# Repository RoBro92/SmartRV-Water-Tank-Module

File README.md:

# SmartRV Water Tank Module
**A ESP based water tank module for a Camper/RV**

All feature requests are tracked in the GitHub issue tracker. 
[Feature Requests](https://github.com/RoBro92/feature-requests/issues)

This water tank module is designed to fill a gap in the market for accessible smart water tank monitoring. Other systems such as Pico and Victron do exist however their cost can be prohibitive and require additional components. This module is based on the ESP8266/32 by Espressif & is designed to work standalone or as part of a network to provide accurate and real-time updates for water tank level and temperature. It also provides a relay designed to interface with motorized ball valves or 2/3 wire and will allow remote draining of tanks without having to leave the vehicle. This not only makes filling the tank easier but can also provide emergency frost protection. 

The beauty of the ESP32 is that it can be easily programmed and by having the extra pins on a header you can add your own inputs/outputs to interface with the board. 

The module has been kept as compact as possible and allows for a direct connection to 12v or 24v vehicle systems. 

**If you want to support the development you can purchase the V1 board as a DIY kit or fully assembled V2  from my Ko-Fi Shop [SmartRV Shop](https://ko-fi.com/smartrv/shop)**

## **I have developed two separate versions of this module**

[V1 is THT and is suitable for at-home soldering](#tht)

[V2 is the final retail product and comes pre assembled inclduing software to allow easy OTA upload](#smd)

### THT

# **V1.3**
This release represents the final revision any further changes should be requested in the [Feature Requests](https://github.com/RoBro92/feature-requests/issues) section. It has been updated to include the design schematic and PCB layout. I will stock a number of these boards to be assembled by yourself and can also include supporting documentation. This device can also be supplied assembled if required. 

# **Changes**
- [x] - Updated to V1.3 final. 

# **Features**
- [x] - Removeable WemosD1 chip (ESP8266)
- [x] - Onboard power regulation
- [x] - Variable voltage input 8v-36v
- [x] - Compact form factor
- [x] - DS18b20 temperature sensor
- [x] - Resistive water level sensor
- [x] - 10A relay for water valve control
- [x] - LED Indicator for Power-ON
- [x] - Added reverse polarity protection
- [x] - Added LED indicators for power and relay
- [x] - Updated repository with Gerber production files

# **Images**
<table>
  <tr>
    <td>3D Model</td>
  </tr>
  <tr>
    <td></td>
  </tr>
 
 </table>
<table>
  <tr>
         <td>Schematic</td>
     <td>PCB Layout</td>

  </tr>
  <tr>
   <td></td>
   <td></td>    
  </tr>
 </table>

<table>
  <tr>
    <td>PCB Front v1.0</td>
     <td>PCB Rear v1.0</td>
  </tr>
  <tr>
    <td></td>
    <td></td>
  </tr>
 </table>

# **WARNING**
This board does not have any fuse protection as such this must be provided externally.

___

### SMD

# **V2.1**
This version is the final retail production of the SmartRV Water Tank Module. It comes with many improvements over the V1 version. 
Built primarily with surface mounted components this version is able to be as compact as possible while also retaining a full feature set. 
This board will be available to buy from my Kofi Shop.

It will also feature an ESP32 Module for several reasons;
- Bluetooth connection with AIO board to act as an additional wireless tank sensor
- Lower power consumption if being used with a battery
- Newer technology

# **Changes This Version**
- [x] - Added 3D printed case

# **Features**
- [x] - ESP32-C3-Mini
- [x] - Onboard power regulation
- [x] - Variable voltage input 8v-36v
- [x] - Compact form factor
- [x] - DS18b20 temperature sensor input
- [x] - Resistive water level sensor input with variable resistance selection via THT resistor
- [x] - 10A relay for water valve control 
- [x] - Reverse polarity protection
- [x] - External display provided via TX/RX for Nextion display
- [x] - Reverse polarity protection
- [x] - Expansion header for user customisation
- [x] - Bluetooth communication built into ESP32 module

# **Planned Changes**

- [ ] - Bluetooth app
- [ ] - Onboard USB programmer
- [ ] - Manual Override switch

# **Images**
<table>
  <tr>
    <td>Schematic</td>
     <td>PCB Layout</td>
  </tr>
  <tr>
    <td></td>
    <td></td>
  </tr>
 </table>

<table>
  <tr>
    <td>3D Model Front</td>
     <td>3D Model Rear</td>
  </tr>
  <tr>
    <td></td>
    <td></td>
  </tr>
 </table>

<table>
  <tr>
    <td>Case</td>
     <td>Case Inside</td>
  </tr>
  <tr>
    <td></td>
    <td></td>
  </tr>
 </table>

# **WARNING**
This board does not have any fuse protection as such this must be provided externally.

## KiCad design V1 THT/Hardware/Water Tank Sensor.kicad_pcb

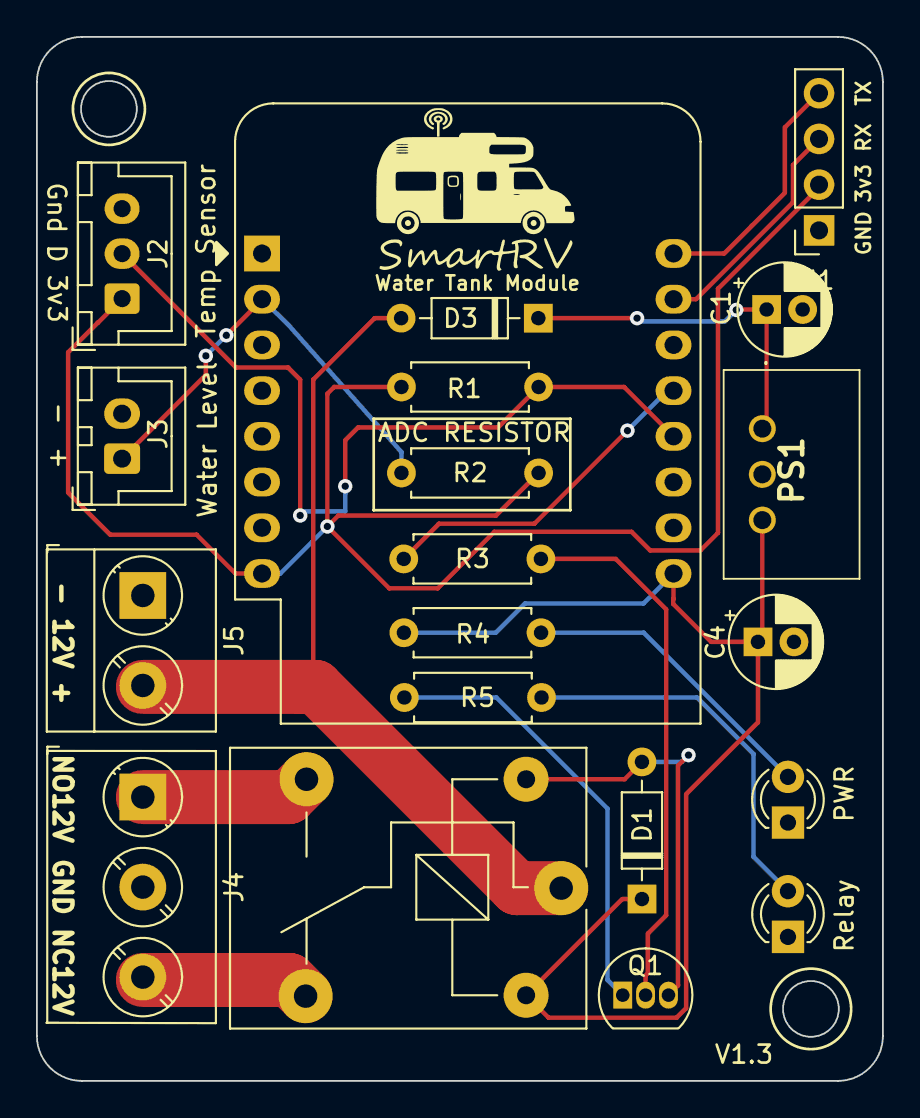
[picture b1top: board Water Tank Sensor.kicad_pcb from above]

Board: 2 copper layers, 47.0 x 58.0 mm, 20 parts (0 on the bottom side), 17 nets.

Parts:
C1: 10uf; CP_Radial_D5.0mm_P2.00mm
C4: 22uf; CP_Radial_D5.0mm_P2.00mm
D1, D3: 1N4148; D_DO-35_SOD27_P7.62mm_Horizontal
D2: Power LED; LED_D3.0mm
D4: Relay; LED_D3.0mm
J1: Programming port; PinSocket_1x04_P2.54mm_Vertical
J2: Temp Sensor; JST_XH_B3B-XH-A_1x03_P2.50mm_Vertical
J3: Water Level; JST_XH_B2B-XH-A_1x02_P2.50mm_Vertical
J4: Valve Terminal; TerminalBlock_Phoenix_PT-1,5-3-5.0-H_1x03_P5.00mm_Horizontal
J5: 12v In; TerminalBlock_Phoenix_PT-1,5-2-5.0-H_1x02_P5.00mm_Horizontal
PS1: K7805-500R3; K7805500R3
Q1: 2N3904; TO-92_Inline
R1: 470; R_Axial_DIN0207_L6.3mm_D2.5mm_P7.62mm_Horizontal
R2: 4.7k; R_Axial_DIN0207_L6.3mm_D2.5mm_P7.62mm_Horizontal
R3: 1.5k; R_Axial_DIN0207_L6.3mm_D2.5mm_P7.62mm_Horizontal
R4, R5: 10k; R_Axial_DIN0207_L6.3mm_D2.5mm_P7.62mm_Horizontal
Relay1: Relay; Relay_SPDT_SANYOU_SRD_Series_Form_C
U1: WeMos_D1_mini; WEMOS_D1_mini_light

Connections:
+3V3: J1.2, J2.1, R1.1, R2.1, U1.8 (3V3)
+5V: C4.1, D1.1 (K), PS1.3 (VO), R4.1, Relay1.5, U1.9 (5V)
+12V: D3.2 (A), J5.2, Relay1.1
/ADC1: J3.1, R2.2, U1.2 (A0)
/Relay: R3.1, U1.13 (SDA/D2)
/Temp: J2.2, R1.2, U1.12 (D3)
/rx: J1.3, U1.15 (RX)
/tx: J1.4, U1.16 (TX)
GND: C1.2, C4.2, D2.1 (K), D4.1 (K), J1.1, J2.3, J3.2, J4.2, J5.1, PS1.2 (GND), U1.10 (GND)
unnamed: C1.1, D3.1 (K), PS1.1 (VIN)
unnamed: D1.2 (A), Q1.3 (C), Relay1.2
unnamed: D2.2 (A), R4.2
unnamed: D4.2 (A), R5.1
unnamed: J4.1, Relay1.3
unnamed: J4.3, Relay1.4
unnamed: Q1.1 (E), R5.2
unnamed: Q1.2 (B), R3.2

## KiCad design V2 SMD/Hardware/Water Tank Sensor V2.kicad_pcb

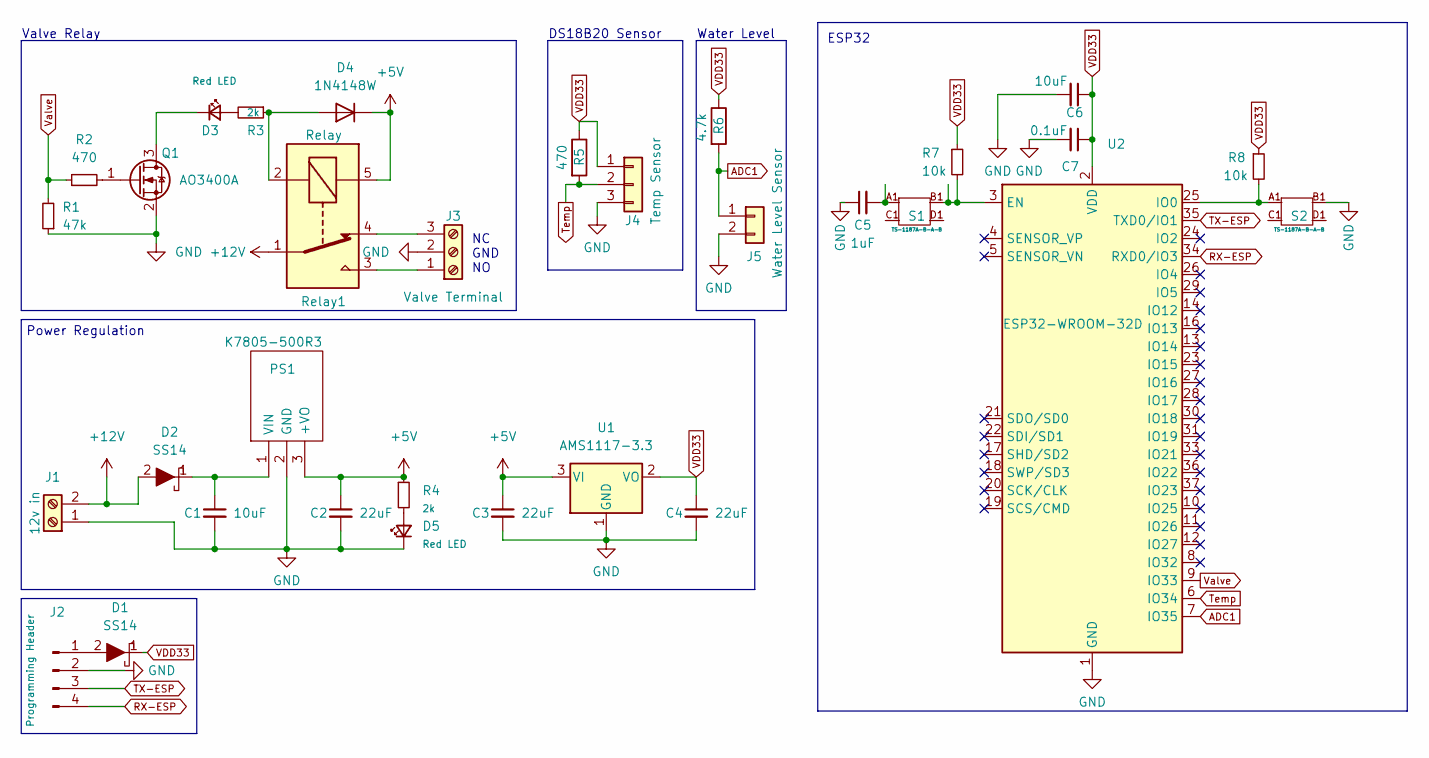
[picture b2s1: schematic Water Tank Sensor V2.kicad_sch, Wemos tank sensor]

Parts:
C1: 10uF; C_0805_2012Metric; Voltage 50v
C2, C3, C4: 22uF; C_0805_2012Metric; Voltage 10v
C5: 1uF; C_0805_2012Metric
C6: 10uF; C_0805_2012Metric
C7: 0.1uF; C_0805_2012Metric
D1, D2: SS14; DIOM5126X250N; Manufacturer_Part_Number SS14; Mouser Part Number 821-SS14
D3, D5: Red LED; LED_0805_2012Metric
D4: 1N4148W; D_SOD-123
J1: 12v in; TerminalBlock_Phoenix_MKDS-1,5-2_1x02_P5.00mm_Horizontal
J2: Programming Header; PinHeader_1x04_P2.54mm_Vertical
J3: Valve Terminal; TerminalBlock_Phoenix_MKDS-1,5-3_1x03_P5.00mm_Horizontal
J4: Temp Sensor; JST_XH_S3B-XH-A-1_1x03_P2.50mm_Horizontal
J5: Water Level Sensor; JST_XH_S2B-XH-A-1_1x02_P2.50mm_Horizontal
PS1: K7805-500R3; K7805500R3; Manufacturer_Part_Number K7805-500R3
Q1: AO3400A; SOT-23
R1: 47k; R_0805_2012Metric
R2, R5: 470; R_0805_2012Metric
R3, R4: 2k; R_0805_2012Metric
R6: 4.7k; R_0805_2012Metric
R7, R8: 10k; R_0805_2012Metric
Relay1: Relay; Relay_SPDT_SANYOU_SRD_Series_Form_C
S1, S2: TS-1187A-B-A-B; TS1187ABAB; Manufacturer_Part_Number TS-1187A-B-A-B
U1: AMS1117-3.3; SOT-223-3_TabPin2
U2: ESP32-WROOM-32D; ESP32-WROOM-32

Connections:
+5V: C2.1, C3.1, D4.1 (K), PS1.3 (+VO), R4.1, Relay1.5, U1.3 (VI)
+12V: D2.2, J1.2, Relay1.1
ADC1: J5.1, R6.2, U2.7 (IO35)
GND: C1.2, C2.2, C3.2, C4.2, C5.1, C6.2, C7.2, D5.1 (K), J1.1, J2.2, J3.2, J4.3, J5.2, PS1.2 (GND), Q1.2 (S), R1.1, S2.B1, U1.1 (GND), U2.1 (GND), U2.15 (GND), U2.38 (GND), U2.39 (GND)
unnamed: C1.1, D2.1, PS1.1 (VIN)
unnamed: C5.2, S1.A1
unnamed: D1.2, J2.1
unnamed: D3.1 (K), Q1.3 (D)
unnamed: D3.2 (A), R3.2
unnamed: D4.2 (A), R3.1, Relay1.2
unnamed: D5.2 (A), R4.2
unnamed: J3.1, Relay1.3
unnamed: J3.3, Relay1.4
unnamed: Q1.1 (G), R2.2
unnamed: R7.2, S1.B1, U2.3 (EN)
unnamed: R8.2, S2.A1, U2.25 (IO0)
RX-ESP: J2.4, U2.34 (RXD0/IO3)
TX-ESP: J2.3, U2.35 (TXD0/IO1)
Temp: J4.2, R5.2, U2.6 (IO34)
VDD33: C4.1, C6.1, C7.1, D1.1, J4.1, R5.1, R6.1, R7.1, R8.1, U1.2 (VO), U2.2 (VDD)
Valve: R1.2, R2.1, U2.9 (IO33)

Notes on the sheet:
DS18B20 Sensor
NC GND NO
Water Level
Power Regulation
ESP32
Valve Relay

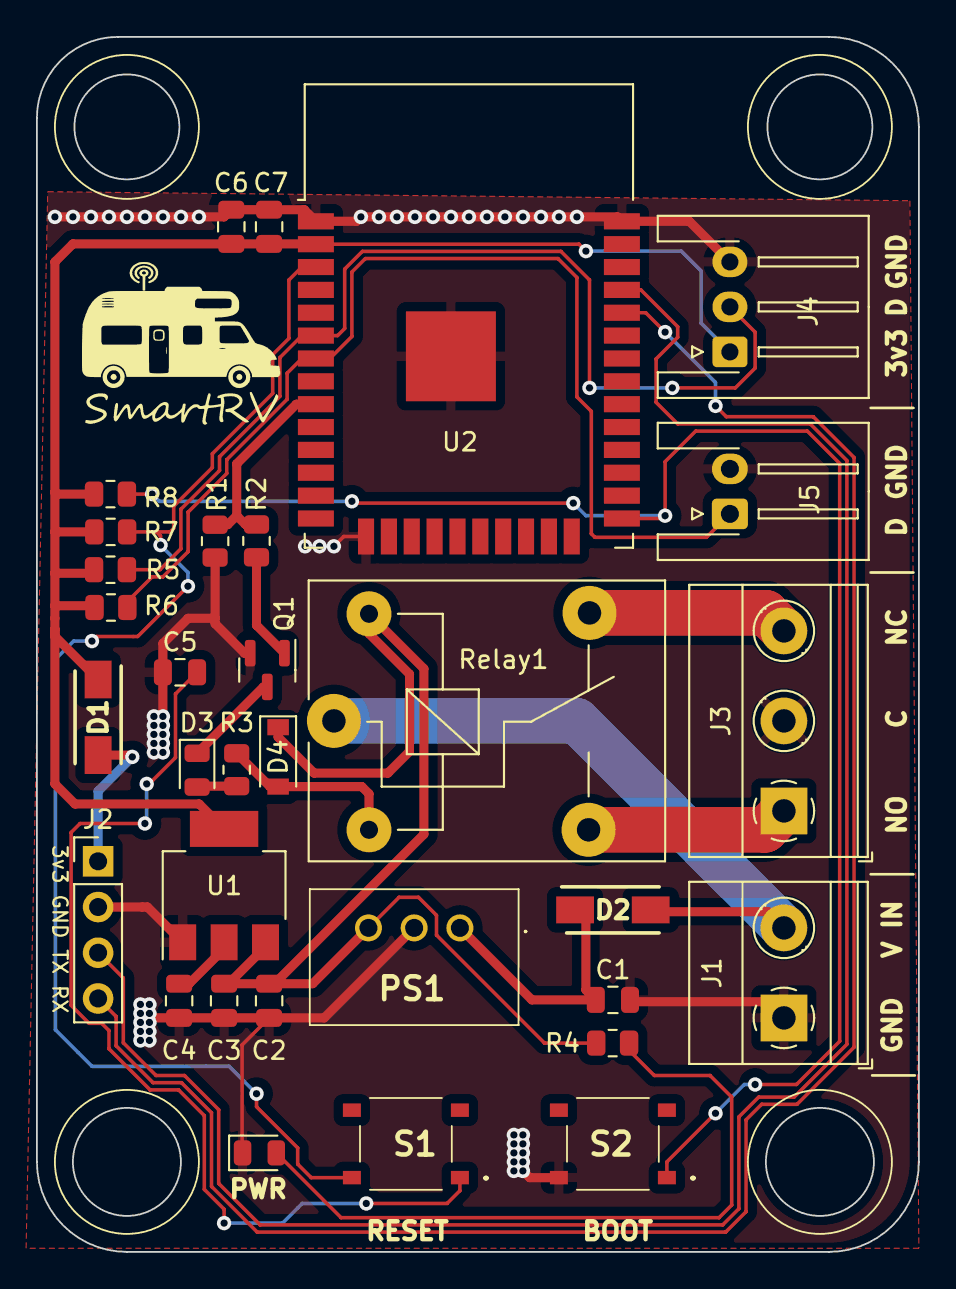
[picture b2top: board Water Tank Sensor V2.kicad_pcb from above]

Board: 2 copper layers, 49.0 x 67.5 mm, 32 parts (0 on the bottom side), 21 nets.

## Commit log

2022-02-17 upload pcb images
    Images of v1.0 pcb uploaded
2022-02-17 Update README.md
    Added images for v1.0 pcb
2022-02-19 Added gitignore
2022-02-23 Images for schematic and PCB uploaded
2022-02-23 Schematic updated
2022-03-01 Added schematic and pcb layout files and included documentation for SMD V2
2022-03-01 added
2022-03-01 Update README.md
    Updated readme to reference new folder locations
2022-03-01 Schematic update
2022-03-02 Added schematic image
2022-03-02 Create LICENSE
    Added License
2022-03-02 Create LICENSE
2022-03-04 Added completed PCB layout for V2SMD with images
2022-03-04 Updated firmware for THT ESPhome
2022-03-15 Update README.md
    Updated v2.0 SMD to be standalone production
2022-04-21 Updated files to v1.1 incnluding images annotating resistor to vary depending on ADC sensor.
2022-04-21 Updated files for V1.1 including images
2022-04-27 Updated v1.2
2022-10-09 New Update SMD to V2.1
    Updated SMD version, Now using Autodesk Fusion360 for PCB design, updated images and readme. Production files to follow once tested
2022-10-11 Update to SMD version
    Including case design and revised sections
2022-10-25 Updated V1 THT to V1.3
    THT version updated to final model with revisions. No further changes will be made to V1. Boards available to purchase from store
2022-12-15 Image update
    Updated images for v1.3
2023-01-09 Add files via upload
    updated v1 images
